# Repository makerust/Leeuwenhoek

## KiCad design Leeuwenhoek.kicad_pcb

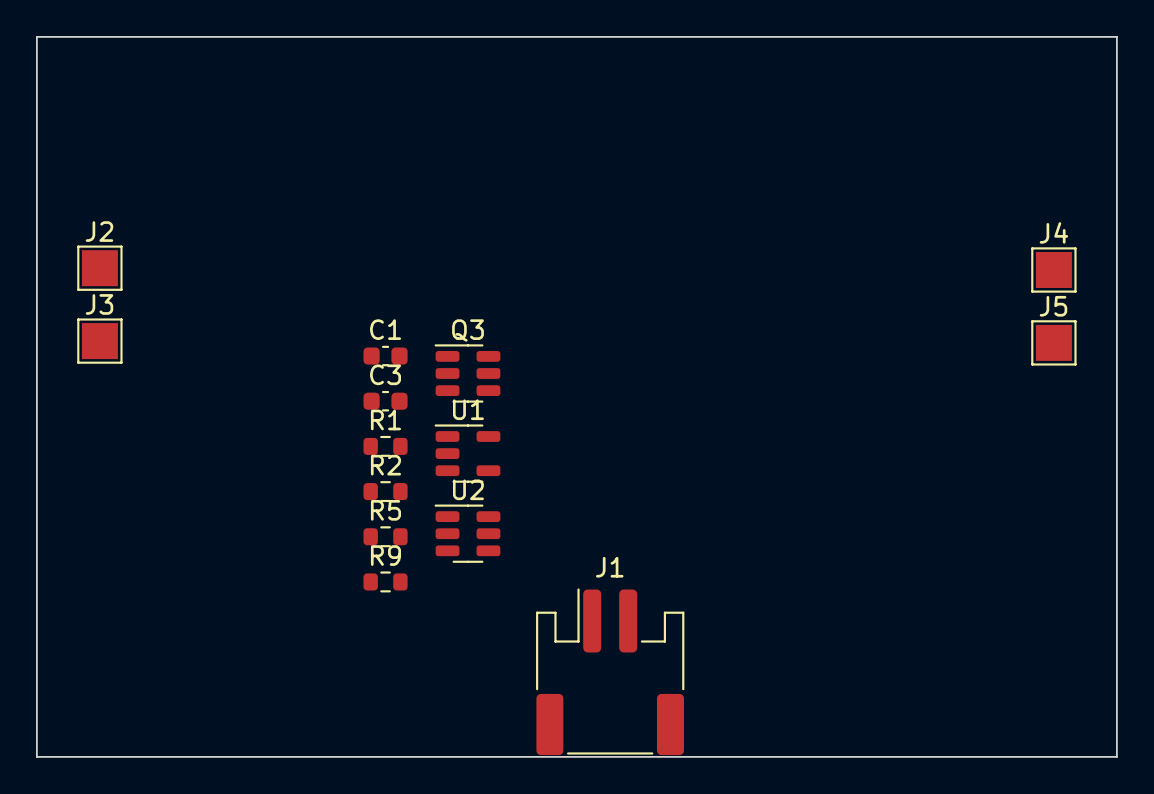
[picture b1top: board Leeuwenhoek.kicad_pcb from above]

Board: 2 copper layers, 60.0 x 40.0 mm, 14 parts (0 on the bottom side), 10 nets, no tracks yet.

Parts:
C1: 100nF; C_0603_1608Metric
C3: 1uF; C_0603_1608Metric
J1: Conn_01x02_Female; JST_PH_S2B-PH-SM4-TB_1x02-1MP_P2.00mm_Horizontal
J2, J3, J4, J5: Conn_01x01_Socket; TestPoint_Pad_2.0x2.0mm
Q3: DMG9926UDM; SOT-23-6
R1: 3k; R_0603_1608Metric
R2: 1k; R_0603_1608Metric
R5: 330R; R_0603_1608Metric
R9: 10k; R_0603_1608Metric
U1: MCP73831-5-OT; SOT-23-5
U2: DW01; SOT-23-6

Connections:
+5V: C3.1, J2.1, R9.2, U1.4 (VDD)
/ChgStat: R9.1, U1.1 (STAT)
/U2_CS: R2.1, U2.2 (CS)
/U2_OC: Q3.6 (G1), U2.3 (OC)
/U2_OD: Q3.4 (G2), U2.1 (OD)
/VBat+: J1.1, J5.1, R5.2, U1.3 (VBAT)
/VBat-: C1.2, J1.2, Q3.3 (S2), U2.6 (GND)
GND: C3.2, J3.1, J4.1, Q3.1 (D1), R1.1, R2.2, U1.2 (VSS)
unnamed: R1.2, U1.5 (PROG)
unnamed: C1.1, R5.1, U2.5 (Vcc)

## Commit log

2024-04-02 second try
